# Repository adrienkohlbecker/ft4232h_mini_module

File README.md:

# FT4232H Mini Module Breakout

A breakout board for FTDI's FT4232H Mini Module. The size is friendly for breadboard use, with two rows of holes left available on each side of the breadboard for wires to come in.

## Board

## Schematic

## BOM

| Refs | Qty | Component | Description |
| ----- | --- | ---- | ----------- |
| C1 | 1 | 100n | Ceramic capacitor, SMD 0805 |
| D1, D2, D3, D4, D5, D6, D7, D8 | 8 | LED | Light emitting diode, SMD 0805 |
| J1, J2 | 2 | Conn_01x20 | Generic connector, single row, 01x20 |
| R1 | 1 | 2.7k | Resistor, SMD 0805 |
| R2, R3, R4, R5, R6, R7, R8, R9 | 8 | R | Resistor, SMD 0805. Value depends on chosen LED |
| U1 | 1 | 74HC595 | 8-bit serial in/out Shift Register 3-State Outputs SOIC-16 |
| U2 | 1 | FT4232H-56Q_MINI_MDL | FT4232H Mini Module, or two 2x13 Dupont sockets |

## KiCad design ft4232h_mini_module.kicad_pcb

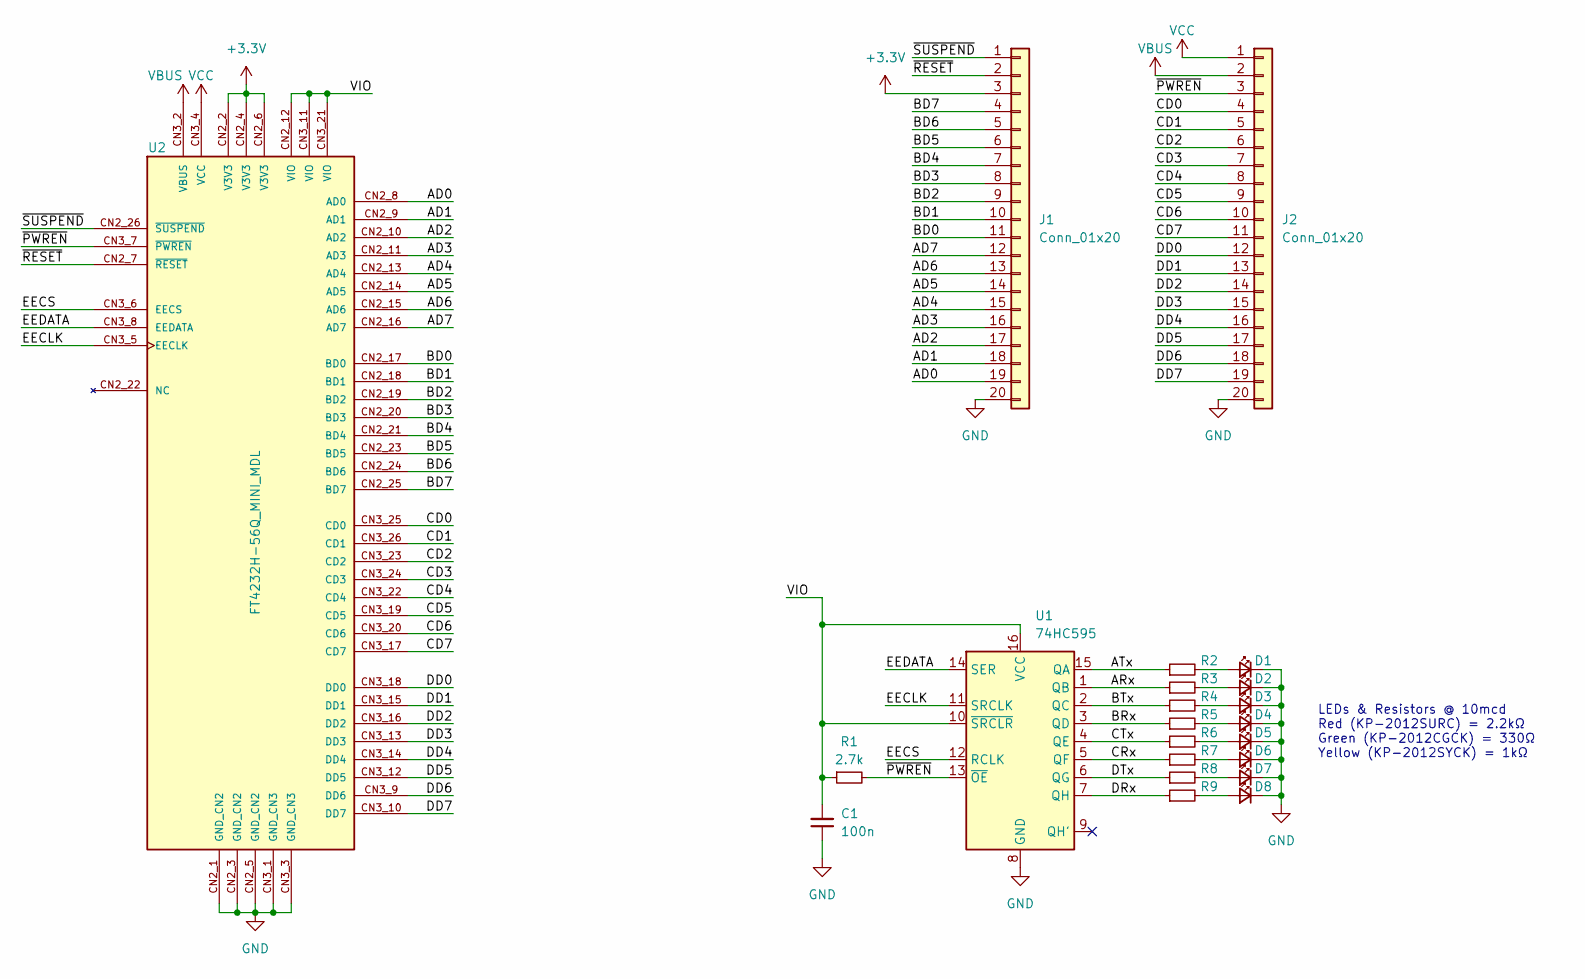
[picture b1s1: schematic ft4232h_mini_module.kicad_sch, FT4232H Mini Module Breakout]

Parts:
C1: 100n; C_0805_2012Metric_Pad1.18x1.45mm_HandSolder
D1, D2, D3, D4, D5, D6, D7, D8: LED; LED_0805_2012Metric_Pad1.15x1.40mm_HandSolder
J1, J2: Conn_01x20; PinHeader_1x20_P2.54mm_Vertical
R1: 2.7k; R_0805_2012Metric_Pad1.20x1.40mm_HandSolder
R2, R3, R4, R5, R6, R7, R8, R9: R; R_0805_2012Metric_Pad1.20x1.40mm_HandSolder
U1: 74HC595; SOIC-16_3.9x9.9mm_P1.27mm
U2: FT4232H-56Q_MINI_MDL; MODULE_FT4232H-56Q_MINI_MDL

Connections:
+3.3V: J1.3, U2.CN2_2 (V3V3), U2.CN2_4 (V3V3), U2.CN2_6 (V3V3)
/AD0: J1.19, U2.CN2_8 (AD0)
/AD1: J1.18, U2.CN2_9 (AD1)
/AD2: J1.17, U2.CN2_10 (AD2)
/AD3: J1.16, U2.CN2_11 (AD3)
/AD4: J1.15, U2.CN2_13 (AD4)
/AD5: J1.14, U2.CN2_14 (AD5)
/AD6: J1.13, U2.CN2_15 (AD6)
/AD7: J1.12, U2.CN2_16 (AD7)
/ARx: R3.1, U1.1 (QB)
/ATx: R2.1, U1.15 (QA)
/BD0: J1.11, U2.CN2_17 (BD0)
/BD1: J1.10, U2.CN2_18 (BD1)
/BD2: J1.9, U2.CN2_19 (BD2)
/BD3: J1.8, U2.CN2_20 (BD3)
/BD4: J1.7, U2.CN2_21 (BD4)
/BD5: J1.6, U2.CN2_23 (BD5)
/BD6: J1.5, U2.CN2_24 (BD6)
/BD7: J1.4, U2.CN2_25 (BD7)
/BRx: R5.1, U1.3 (QD)
/BTx: R4.1, U1.2 (QC)
/CD0: J2.4, U2.CN3_25 (CD0)
/CD1: J2.5, U2.CN3_26 (CD1)
/CD2: J2.6, U2.CN3_23 (CD2)
/CD3: J2.7, U2.CN3_24 (CD3)
/CD4: J2.8, U2.CN3_22 (CD4)
/CD5: J2.9, U2.CN3_19 (CD5)
/CD6: J2.10, U2.CN3_20 (CD6)
/CD7: J2.11, U2.CN3_17 (CD7)
/CRx: R7.1, U1.5 (QF)
/CTx: R6.1, U1.4 (QE)
/DD0: J2.12, U2.CN3_18 (DD0)
/DD1: J2.13, U2.CN3_15 (DD1)
/DD2: J2.14, U2.CN3_16 (DD2)
/DD3: J2.15, U2.CN3_13 (DD3)
/DD4: J2.16, U2.CN3_14 (DD4)
/DD5: J2.17, U2.CN3_12 (DD5)
/DD6: J2.18, U2.CN3_9 (DD6)
/DD7: J2.19, U2.CN3_10 (DD7)
/DRx: R9.1, U1.7 (QH)
/DTx: R8.1, U1.6 (QG)
/EECLK: U1.11 (SRCLK), U2.CN3_5 (EECLK)
/EECS: U1.12 (RCLK), U2.CN3_6 (EECS)
/EEDATA: U1.14 (SER), U2.CN3_8 (EEDATA)
/VIO: C1.2, R1.1, U1.10 (~SRCLR), U1.16 (VCC), U2.CN2_12 (VIO), U2.CN3_11 (VIO), U2.CN3_21 (VIO)
/~PWREN: J2.3, R1.2, U1.13 (~OE), U2.CN3_7 (~PWREN)
/~RESET: J1.2, U2.CN2_7 (~RESET)
/~SUSPEND: J1.1, U2.CN2_26 (~SUSPEND)
GND: C1.1, D1.1 (K), D2.1 (K), D3.1 (K), D4.1 (K), D5.1 (K), D6.1 (K), D7.1 (K), D8.1 (K), J1.20, J2.20, U1.8 (GND), U2.CN2_1 (GND_CN2), U2.CN2_3 (GND_CN2), U2.CN2_5 (GND_CN2), U2.CN3_1 (GND_CN3), U2.CN3_3 (GND_CN3)
unnamed: D1.2 (A), R2.2
unnamed: D2.2 (A), R3.2
unnamed: D3.2 (A), R4.2
unnamed: D4.2 (A), R5.2
unnamed: D5.2 (A), R6.2
unnamed: D6.2 (A), R7.2
unnamed: D7.2 (A), R8.2
unnamed: D8.2 (A), R9.2
VBUS: J2.2, U2.CN3_2 (VBUS)
VCC: J2.1, U2.CN3_4 (VCC)

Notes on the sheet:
LEDs & Resistors @ 10mcd Red (KP-2012SURC) = 2.2kΩ Green (KP-2012CGCK) = 330Ω Yellow (KP-2012SYCK) = 1kΩ

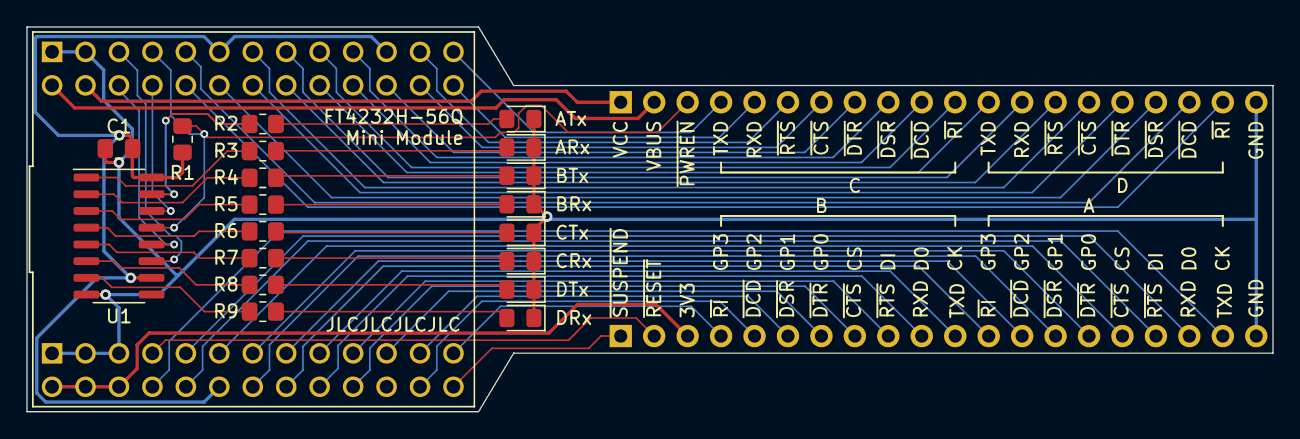
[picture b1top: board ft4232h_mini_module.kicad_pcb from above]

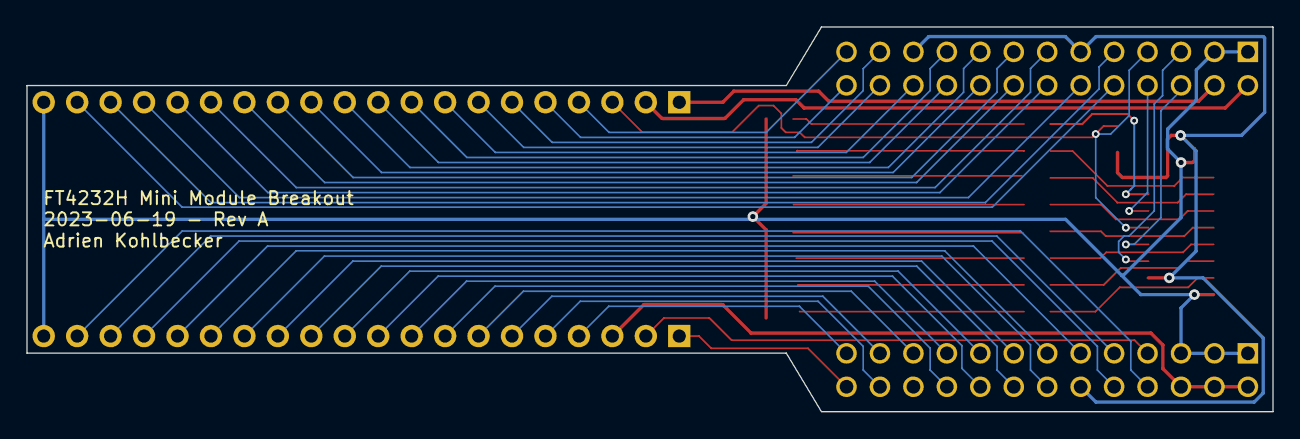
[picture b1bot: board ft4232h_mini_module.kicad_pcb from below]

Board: 2 copper layers, 94.6 x 29.2 mm, 22 parts (2 on the bottom side), 59 nets.

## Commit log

2023-06-19 Update template
2023-06-19 First release

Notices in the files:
ft4232h_mini_module.kicad_pcb:
Licensed under CERN-OHL-W v2
Copyright © Adrien Kohlbecker
